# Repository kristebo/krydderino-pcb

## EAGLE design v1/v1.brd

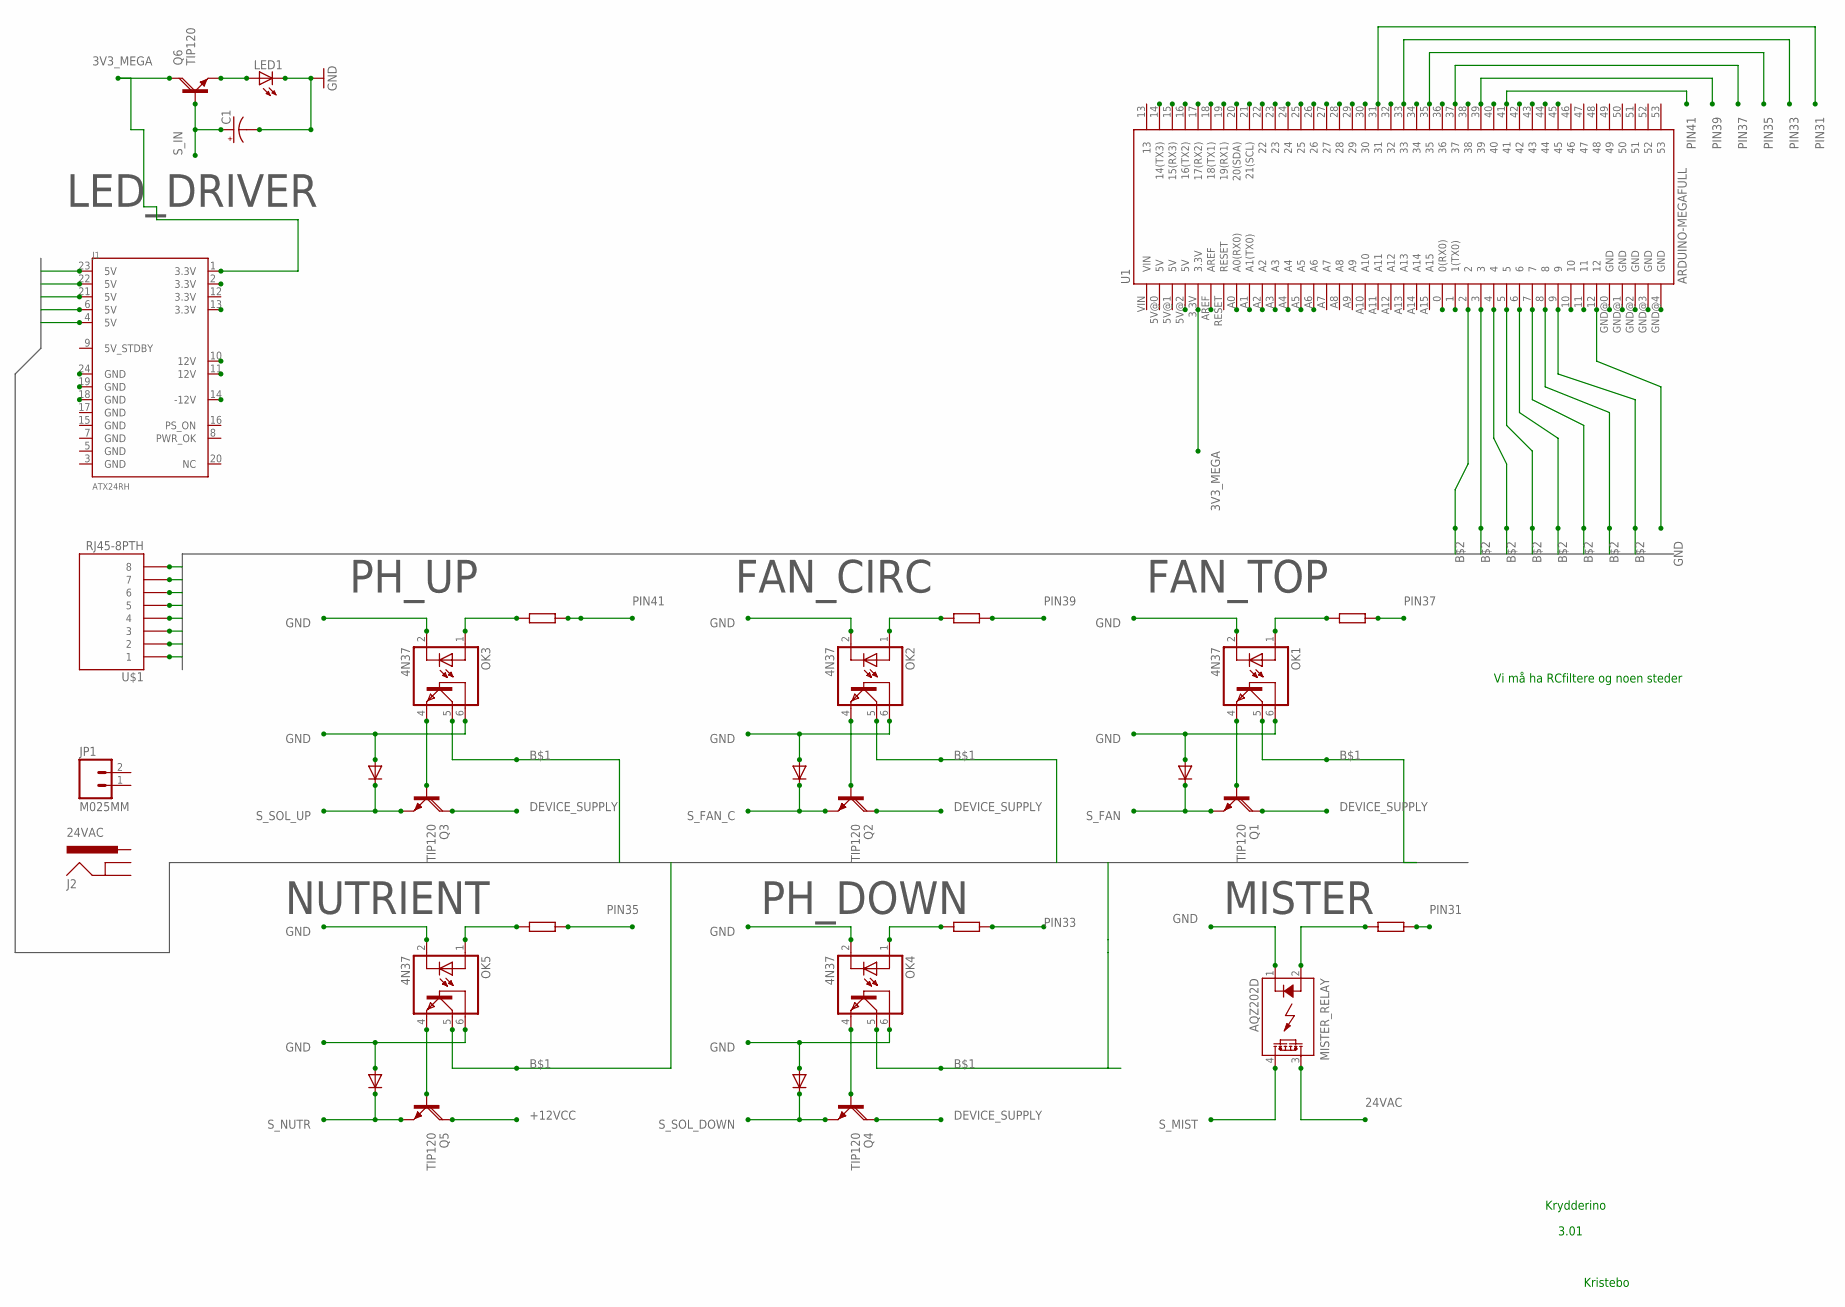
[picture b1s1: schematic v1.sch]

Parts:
C1: CAP_POLPTH1; CPOL-RADIAL-100UF-25V
J1: ATX24RH; ATX24_RIGHT_ANGLE
J2: 24VAC; POWER_JACK_SLOT
JP1: M025MM; SCREWTERMINAL-5MM-2
LED1: LED3MM
MISTER_RELAY: AQZ202D; AQZ-SIL04
OK1, OK2, OK3, OK4, OK5: 4N37; DIL06
Q1, Q2, Q3, Q4, Q5, Q6: TIP120; TO220AH
U1: ARDUINO-MEGAFULL; ARDUINO_MEGA
U$1: RJ45-8PTH; RJ45-8

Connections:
3V3_MEGA: J1.1 (3.3V), Q6.C, U1.3.3V
24VAC: MISTER_RELAY.3 (DS1)
+12VCC: Q5.C
B$2: U1.2, U1.3, U1.4, U1.5, U1.6, U1.7, U1.8, U1.9, U$1.1, U$1.2, U$1.3, U$1.4, U$1.5, U$1.6, U$1.7, U$1.8
DEVICE_SUPPLY: Q1.C, Q2.C, Q3.C, Q4.C
GND: C1.2 (-), LED1.K (C), MISTER_RELAY.1 (K), OK1.2 (C), OK1.6 (BAS), OK2.2 (C), OK2.6 (BAS), OK3.2 (C), OK3.6 (BAS), OK4.2 (C), OK4.6 (BAS), OK5.2 (C), OK5.6 (BAS), U1.12
unnamed: OK1.4 (EMI), Q1.B
unnamed: LED1.A, Q6.E
unnamed: OK2.4 (EMI), Q2.B
unnamed: OK3.4 (EMI), Q3.B
unnamed: OK4.4 (EMI), Q4.B
unnamed: OK5.4 (EMI), Q5.B
PIN31: OK1.1 (A), U1.31
PIN33: OK2.1 (A), U1.33
PIN35: OK3.1 (A), U1.35
PIN37: OK4.1 (A), U1.37
PIN39: OK5.1 (A), U1.39
PIN41: MISTER_RELAY.2 (A), U1.41
S_FAN: Q1.E
S_FAN_C: Q2.E
S_IN: C1.1 (+), Q6.B
S_MIST: MISTER_RELAY.4 (DS2)
S_NUTR: Q5.E
S_SOL_DOWN: Q4.E
S_SOL_UP: Q3.E

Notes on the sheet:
MISTER
FAN_TOP
FAN_CIRC
PH_UP
PH_DOWN
NUTRIENT
LED_DRIVER
Vi må ha RCfiltere og noen steder
Krydderino
3.01
Kristebo

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
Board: 2 copper layers, 19 parts (0 on the bottom side), 18 nets, no tracks yet.

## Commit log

2013-11-15 v3.01
2013-11-15 Framed
    Added a frame, some connectors and resistors on signalpins. These should
    have a pulldown to gnd aswell.
2013-11-15 Last
    Uppdateted text
2013-11-15 last
    more changes to come

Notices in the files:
parts and their libraries:
SparkFun-Boards: Licensing: CC v3.0 Share-Alike You are welcome to use this library for commercial purposes.
